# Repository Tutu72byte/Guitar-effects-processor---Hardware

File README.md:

Complete hardware development of an embedded music signal processing module (Guitar Effect Pedal) from structural block diagram to circuit schematic,
pcb design and generation of manufacturing files using KiCad. The projects consists of:

1) Library Creation: Created dedicated project libraries (TIE2026.kicad_sym and TIE2026.pretty) containing custom schematic symbols and footprints.

2) Schematic design: The circuit diagram contains a Microcontroller, SPI Flash Memory, ADC/DAC audio processing stages,
   an interactive touchscreen interface and a switching power supply (9V in, 5V and 3.3V converters and regulators and a 2.5V bias).
   Incorporated specific JTAG and power rail test pads for hardware debugging.

3) PCB Topology & Stack-up: Configured a 4-layer board stack-up (1.6mm total thickness)
   featuring controlled trace spacing (0.1mm) and a dedicated internal ground plane split between analog ground (GND_A)
   and digital ground (GND), thus managing a low-noise layout by segregating the analog circuitry onto the analog ground plane linked via the 10m-Ohms shunt R28.

4) Routing for High-Speed Signals & Impedance Control: Implemented single-ended 50 Ohms data lines for the Flash
   memory and 100 Ohms differential lines for the video interface.

5) Manufacturing Output: Generated industry-standard production packages, including extended
   Gerber files, Drill files, a Pick-and-Place component file and a Bill of Materials (BOM).

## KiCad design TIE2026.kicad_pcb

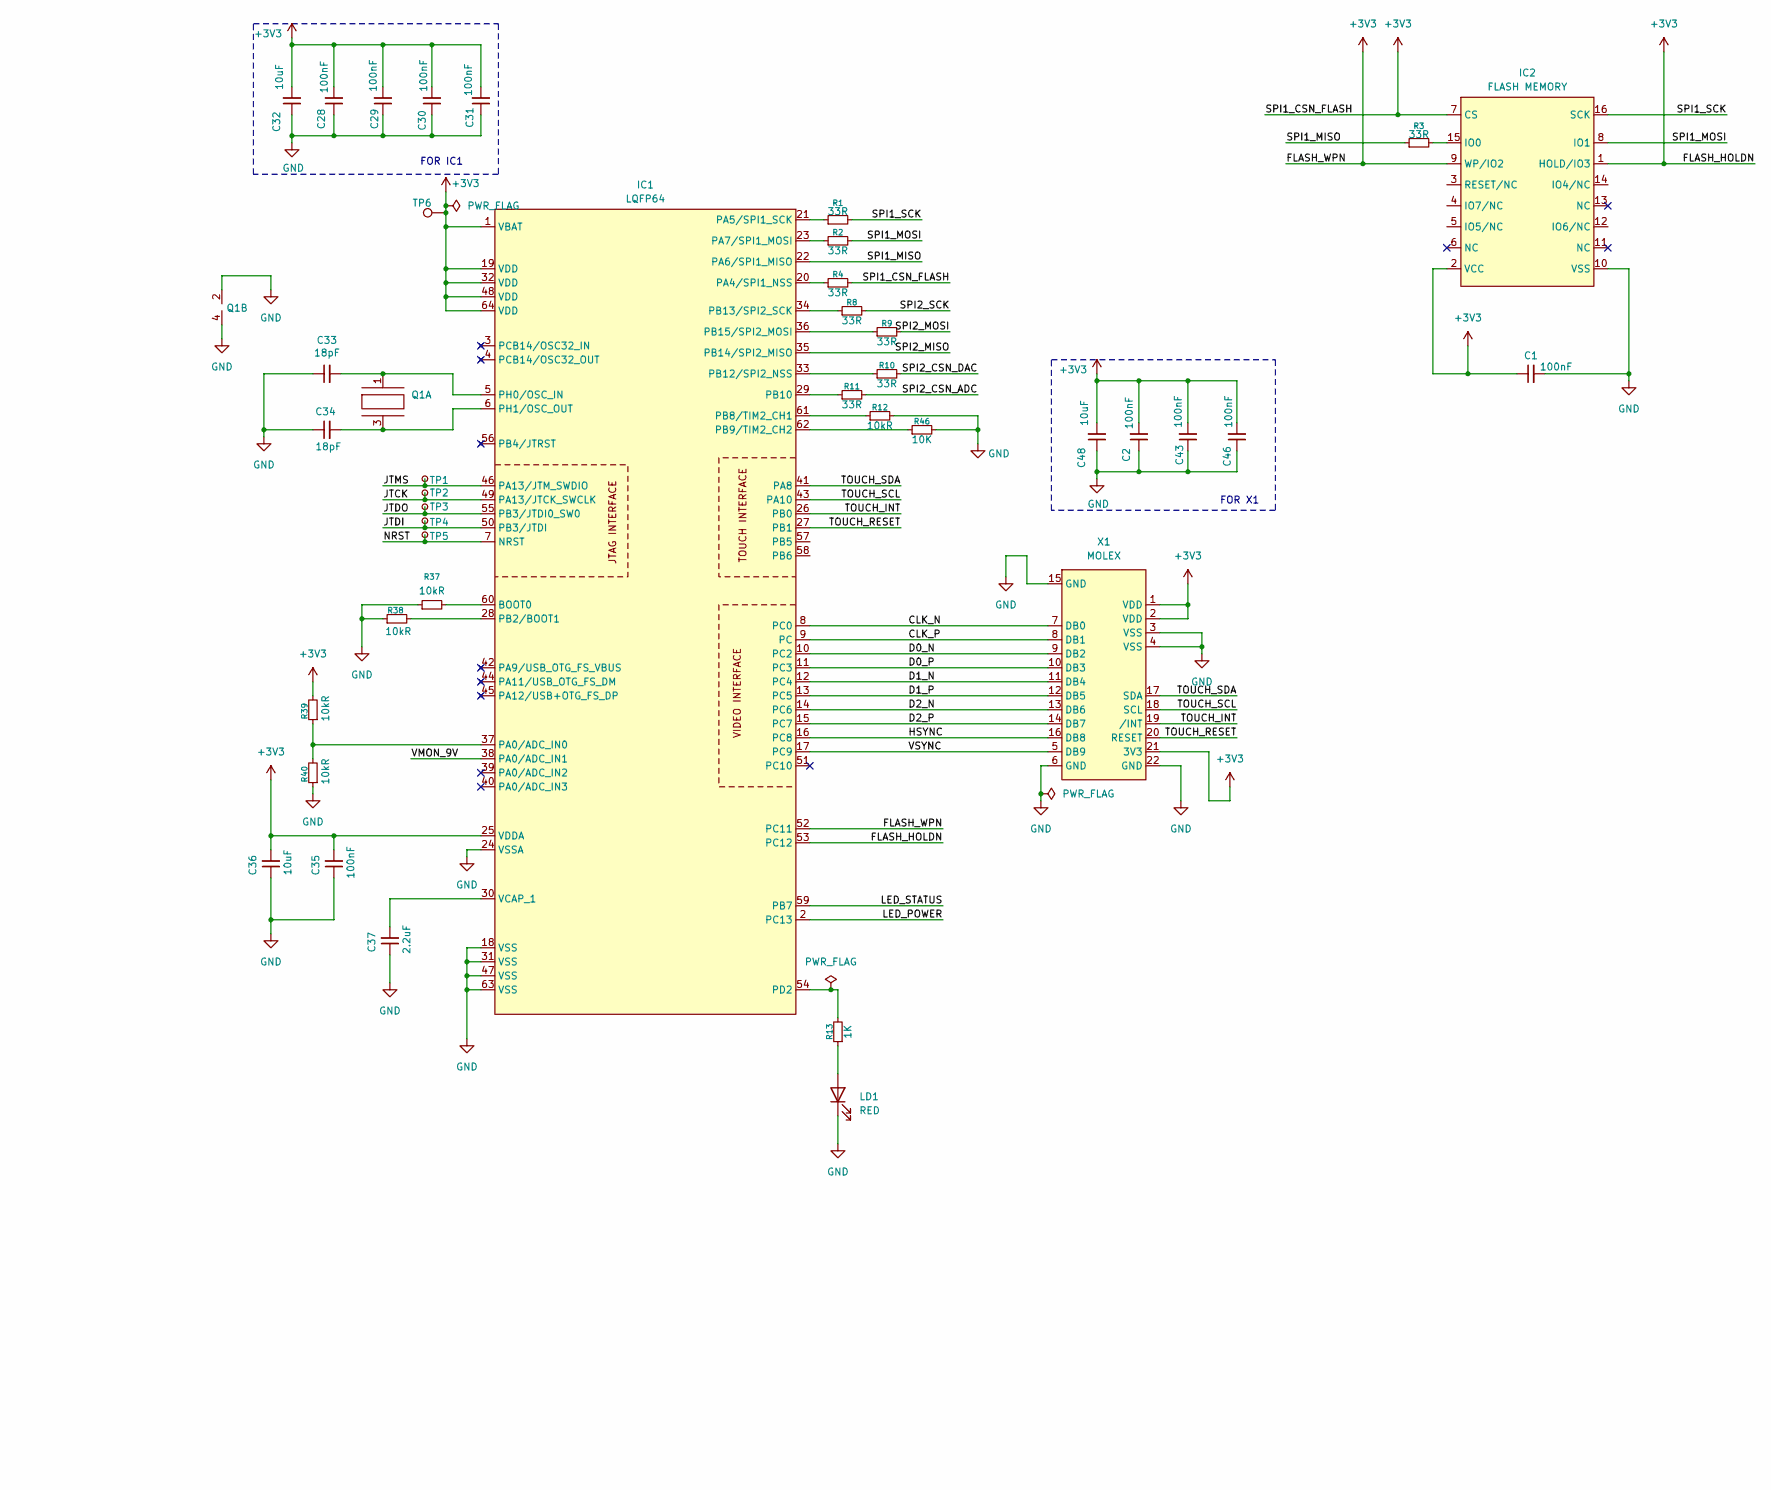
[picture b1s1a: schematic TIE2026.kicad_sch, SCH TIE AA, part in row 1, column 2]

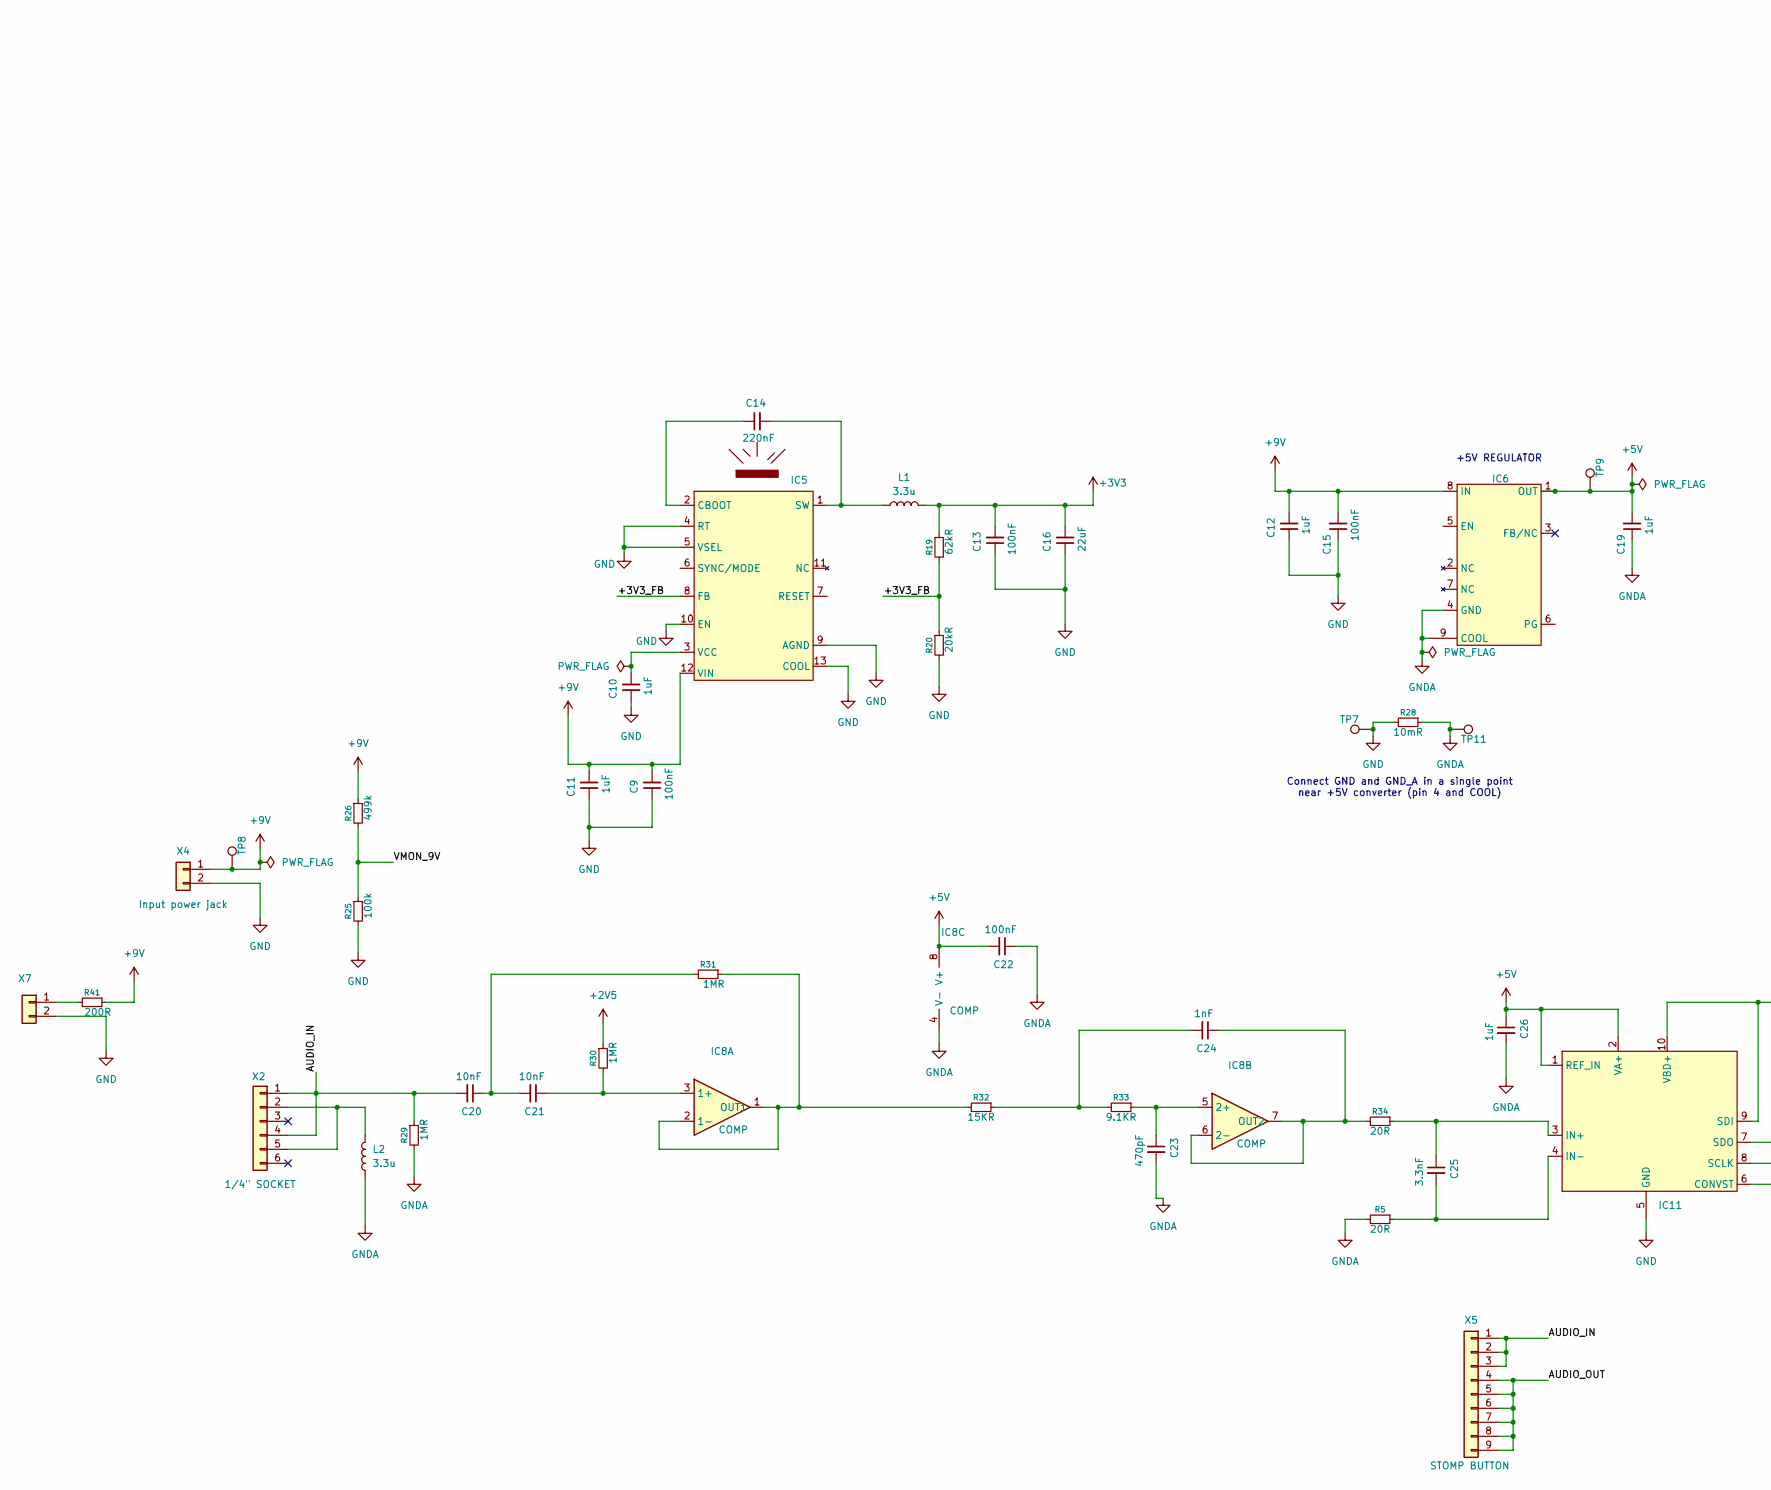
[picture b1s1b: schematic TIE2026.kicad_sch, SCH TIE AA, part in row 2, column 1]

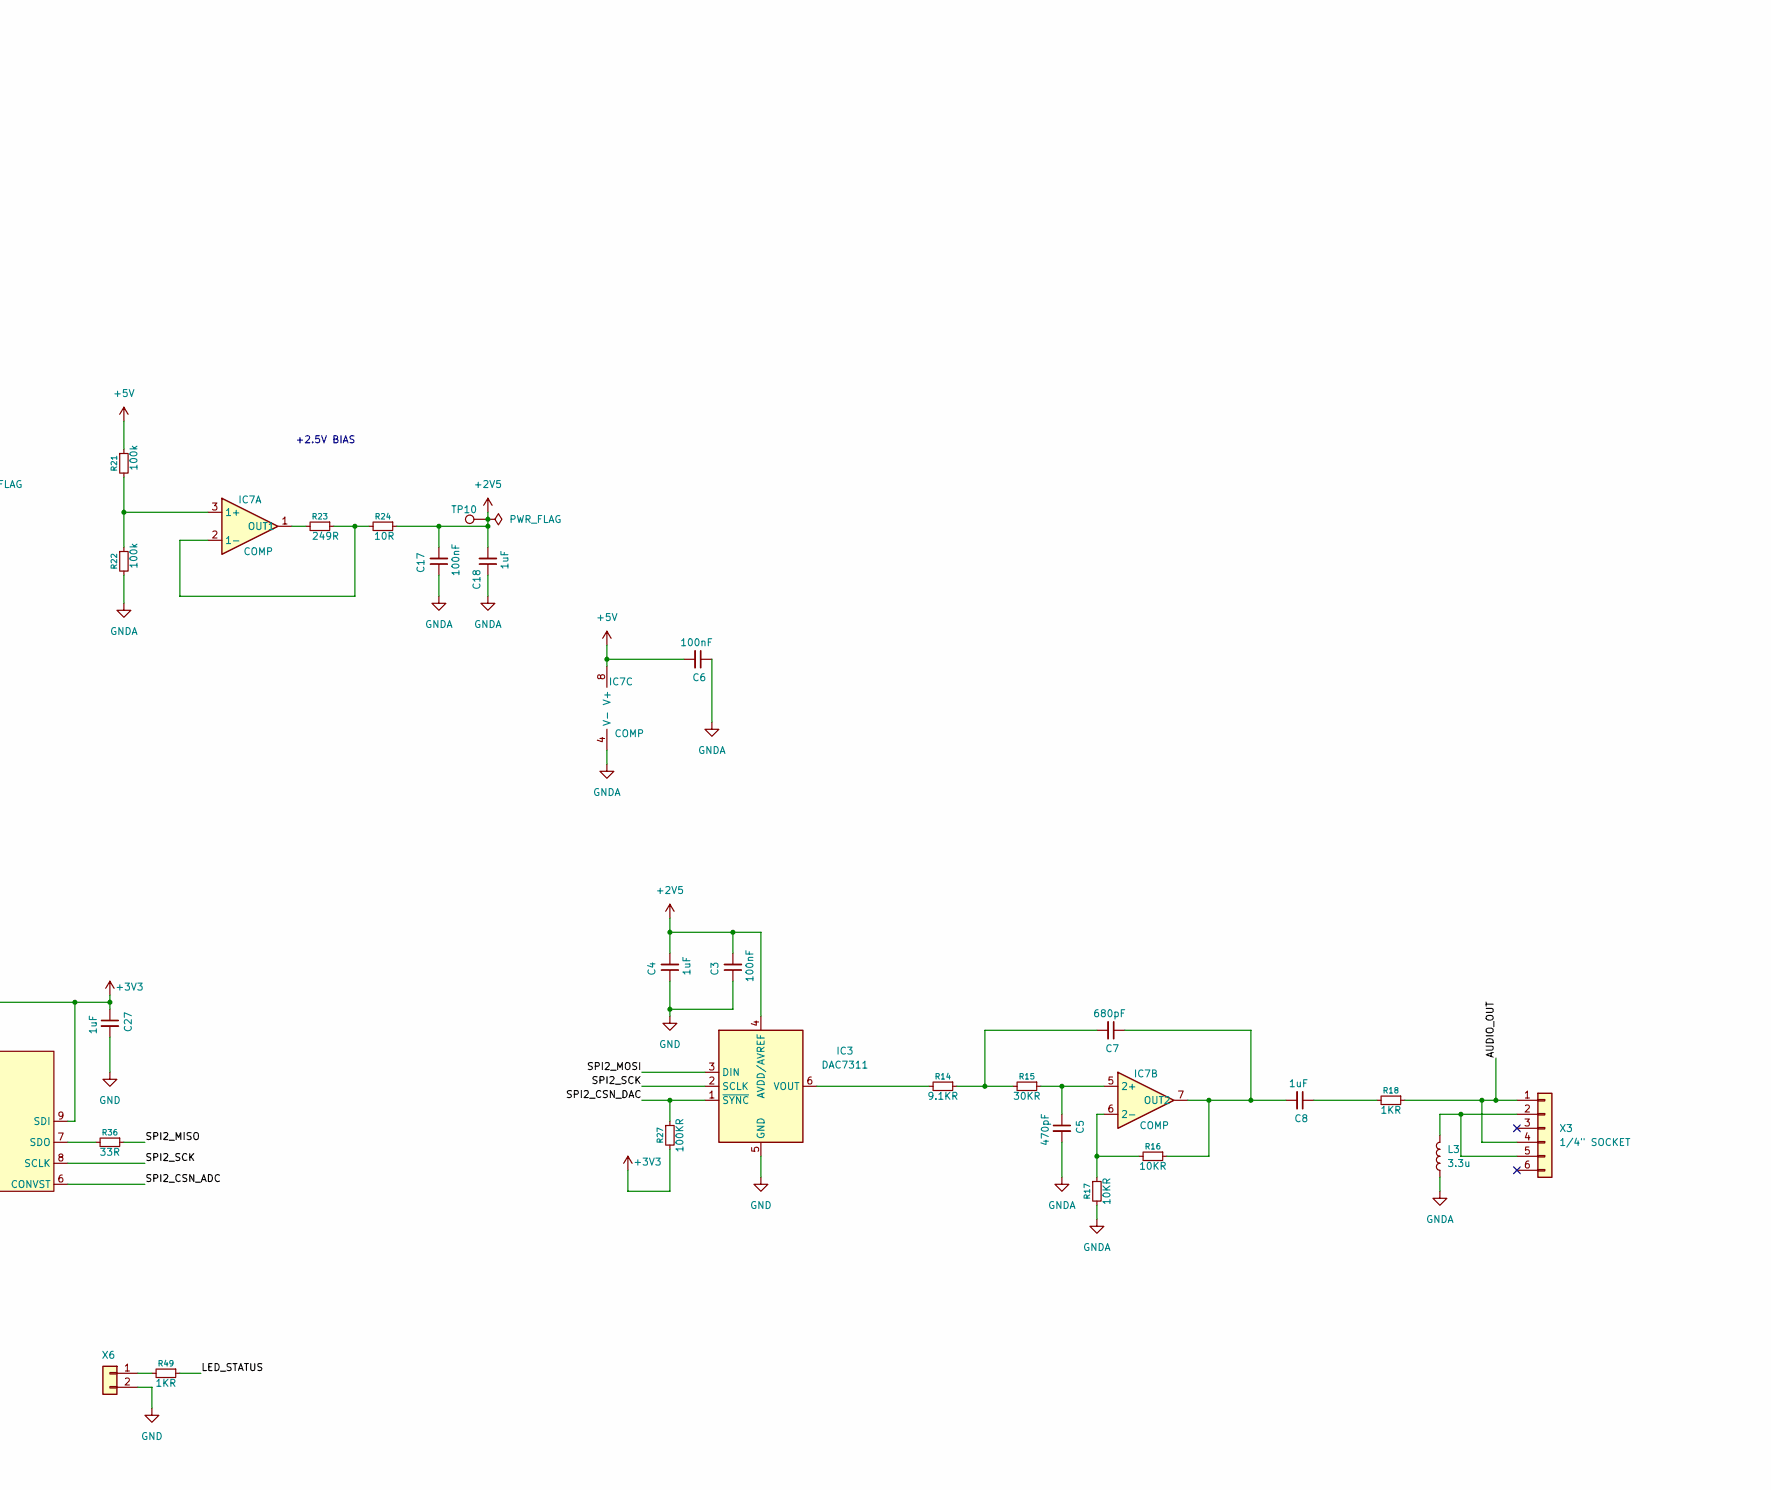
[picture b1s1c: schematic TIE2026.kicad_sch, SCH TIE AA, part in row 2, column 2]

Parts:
C1, C2, C3, C6, C9, C13, C15, C17, C22, C28, C29, C30, C31, C35, C43, C46: 100nF; C_01005_0402Metric
C4, C10, C12, C18, C19, C26, C27: 1uF; C_0805_2012Metric
C5, C23: 470pF; C_01005_0402Metric
C7: 680pF; C_0201_0603Metric
C8: 1uF; C_1206_3216Metric
C11: 1uF; C_1210_3225Metric
C14: 220nF; C_0201_0603Metric
C16: 22uF; C_1210_3225Metric
C20, C21: 10nF; C_0201_0603Metric
C24: 1nF; C_01005_0402Metric
C25: 3.3nF; C_01005_0402Metric
C32, C36, C48: 10uF; C_0201_0603Metric
C33, C34: 18pF; C_0201_0603Metric
C37: 2.2uF; C_0201_0603Metric
IC1: LQFP64; IC1_LQFP64
IC2: FLASH MEMORY; IC2_SO16
IC3: DAC7311; IC3_TSOP6
IC5: IC5_WSON12
IC6: TPS74501PQWDRBRQ1; IC6_SONB
IC7, IC8: COMP; 8AB_PDS08
IC11: IC11_VSSOP
L1: 3.3u; L1_NRS5040
L2, L3: 3.3u; L_0201_0603Metric
LD1: RED; LD1_PLCC
Q1: Q1_NX3225
R1, R2, R3, R4, R8, R9, R10, R11, R36: 33R; R_0402_1005Metric
R5, R34: 20R; R_0402_1005Metric
R12, R37, R38, R39, R40: 10kR; R_0805_2012Metric
R13: 1K; R_0201_0603Metric
R14, R33: 9.1KR; R_0201_0603Metric
R15: 30KR; R_0201_0603Metric
R16, R17: 10KR; R_0805_2012Metric
R18, R49: 1KR; R_0201_0603Metric
R19: 62kR; R_0402_1005Metric
R20: 20kR; R_0402_1005Metric
R21, R22, R25: 100k; R_0201_0603Metric
R23: 249R; R_0201_0603Metric
R24: 10R; R_0201_0603Metric
R26: 499k; R_0201_0603Metric
R27: 100KR; R_0201_0603Metric
R28: 10mR; R_0805_2012Metric
R29, R30, R31: 1MR; R_0805_2012Metric
R32: 15KR; R_0201_0603Metric
R41: 200R; R_0201_0603Metric
R46: 10K; R_0805_2012Metric
TP1, TP2, TP3, TP4, TP5, TP6, TP7, TP8, TP9, TP10, TP11: TEST_POINT_TIE2026
X1: MOLEX; X1_MOLEX
X2, X3: 1/4" SOCKET; QInch_Jack
X4: Input power jack; ADC_021_3
X5: STOMP BUTTON; XC5_MC71101
X6, X7: CONN_2.54; PinHeader_1x02_P2.54mm_Vertical

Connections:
+2V5: C3.2, C4.2, C17.2, C18.2, IC3.4 (AVDD/AVREF), R24.1, R30.1, TP10.1
+3V3: C1.1, C2.2, C13.2, C16.2, C27.1, C28.2, C29.2, C30.2, C31.2, C32.2, C35.2, C36.2, C43.2, C46.2, C48.2, IC1.1 (VBAT), IC1.19 (VDD), IC1.25 (VDDA), IC1.32 (VDD), IC1.48 (VDD), IC1.52 (PC11), IC1.53 (PC12), IC1.64 (VDD), IC2.1 (HOLD/IO3), IC2.2 (VCC), IC2.7 (CS), IC2.9 (WP/IO2), IC11.9 (SDI), IC11.10 (VBD+), L1.2, R4.2, R19.1, R27.2, R39.2, TP6.1, X1.1 (VDD), X1.2 (VDD), X1.21 (3V3)
+5V: C6.2, C19.2, C22.2, C26.1, IC6.1 (OUT), IC7.8 (V+), IC8.8 (V+), IC11.1 (REF_IN), IC11.2 (VA+), R21.1, TP9.1
+9V: C9.2, C11.2, C12.2, C15.2, IC5.12 (VIN), IC6.8 (IN), R26.1, R41.1, TP8.1, X4.1
/+3V3_FB: IC5.8 (FB), R19.2, R20.1
/AUDIO_IN: C20.2, R29.1, X2.1, X2.4, X5.1, X5.2, X5.3
/AUDIO_OUT: R18.1, X3.1, X3.4, X5.4, X5.5, X5.6, X5.7, X5.8, X5.9
/CLK_N: IC1.8 (PC0), X1.7 (DB0)
/CLK_P: IC1.9 (PC), X1.8 (DB1)
/D0_N: IC1.10 (PC2), X1.9 (DB2)
/D0_P: IC1.11 (PC3), X1.10 (DB3)
/D1_N: IC1.12 (PC4), X1.11 (DB4)
/D1_P: IC1.13 (PC5), X1.12 (DB5)
/D2_N: IC1.14 (PC6), X1.13 (DB6)
/D2_P: IC1.15 (PC7), X1.14 (DB7)
/HSYNC: IC1.16 (PC8), X1.16 (DB8)
/JTCK: IC1.49 (PA13/JTCK_SWCLK), TP2.1
/JTDI: IC1.50 (PB3/JTDI), TP4.1
/JTDO: IC1.55 (PB3/JTDI0_SW0), TP3.1
/JTMS: IC1.46 (PA13/JTM_SWDIO), TP1.1
/LED_POWER: IC1.2 (PC13)
/LED_STATUS: IC1.59 (PB7), R49.1
/NRST: IC1.7 (NRST), TP5.1
/SPI1_MISO: IC1.22 (PA6/SPI1_MISO), R3.1
/SPI1_MOSI: IC2.8 (IO1), R2.2
/SPI1_SCK: IC2.16 (SCK), R1.2
/SPI2_CSN_ADC: IC11.6 (CONVST), R11.2
/SPI2_CSN_DAC: IC3.1 (~SYNC), R10.2, R27.1
/SPI2_MISO: IC1.35 (PB14/SPI2_MISO), R36.1
/SPI2_MOSI: IC3.3 (DIN), R9.2
/SPI2_SCK: IC3.2 (SCLK), IC11.8 (SCLK), R8.2
/TOUCH_INT: IC1.26 (PB0), X1.19 (/INT)
/TOUCH_RESET: IC1.27 (PB1), X1.20 (RESET)
/TOUCH_SCL: IC1.43 (PA10), X1.18 (SCL)
/TOUCH_SDA: IC1.41 (PA8), X1.17 (SDA)
/VMON_9V: IC1.38 (PA0/ADC_IN1), R25.1, R26.2
/VSYNC: IC1.17 (PC9), X1.5 (DB9)
GND: C1.2, C2.1, C3.1, C4.1, C9.1, C10.1, C11.1, C12.1, C13.1, C15.1, C16.1, C27.2, C28.1, C29.1, C30.1, C31.1, C32.1, C33.1, C34.1, C35.1, C36.1, C37.1, C43.1, C46.1, C48.1, IC1.18 (VSS), IC1.24 (VSSA), IC1.31 (VSS), IC1.47 (VSS), IC1.63 (VSS), IC2.10 (VSS), IC3.5 (GND), IC5.4 (RT), IC5.5 (VSEL), IC5.9 (AGND), IC5.10 (EN), IC5.13 (COOL), IC11.5 (GND), LD1.1 (K), Q1.2, Q1.4, R12.2, R20.2, R25.2, R28.2, R37.1, R38.1, R40.1, R46.2, TP7.1, X1.3 (VSS), X1.4 (VSS), X1.6 (GND), X1.15 (GND), X1.22 (GND), X4.2, X6.2, X7.2
GNDA: C5.2, C6.1, C17.1, C18.1, C19.1, C22.1, C23.2, C26.2, IC6.4 (GND), IC6.9 (COOL), IC7.4 (V-), IC8.4 (V-), L2.1, L3.1, R5.2, R17.2, R22.2, R28.1, R29.2, TP11.1
unnamed: C7.2, R14.1, R15.2
unnamed: C8.1, R18.2
unnamed: C20.1, C21.2, R31.2
unnamed: C24.2, R32.1, R33.2
unnamed: IC1.60 (BOOT0), R37.2
unnamed: IC1.37 (PA0/ADC_IN0), R39.1, R40.2
unnamed: IC1.20 (PA4/SPI1_NSS), R4.1
unnamed: IC1.21 (PA5/SPI1_SCK), R1.1
unnamed: IC1.23 (PA7/SPI1_MOSI), R2.1
unnamed: IC1.28 (PB2/BOOT1), R38.2
unnamed: IC1.61 (PB8/TIM2_CH1), R12.1
unnamed: IC1.62 (PB9/TIM2_CH2), R46.1
unnamed: IC1.29 (PB10), R11.1
unnamed: IC1.33 (PB12/SPI2_NSS), R10.1
unnamed: IC1.34 (PB13/SPI2_SCK), R8.1
unnamed: IC1.36 (PB15/SPI2_MOSI), R9.1
unnamed: IC1.54 (PD2), R13.2
unnamed: C33.2, IC1.5 (PH0/OSC_IN), Q1.1
unnamed: C34.2, IC1.6 (PH1/OSC_OUT), Q1.3
unnamed: C37.2, IC1.30 (VCAP_1)
unnamed: IC2.15 (IO0), R3.2
unnamed: IC3.6 (VOUT), R14.2
unnamed: C14.1, IC5.2 (CBOOT)
unnamed: C14.2, IC5.1 (SW), L1.1
unnamed: C10.2, IC5.3 (VCC)
unnamed: IC7.3 (1+), R21.2, R22.1
unnamed: IC7.2 (1-), R23.1, R24.2
unnamed: IC7.1 (OUT1), R23.2
unnamed: C5.1, IC7.5 (2+), R15.1
unnamed: IC7.6 (2-), R16.2, R17.1
unnamed: C7.1, C8.2, IC7.7 (OUT2), R16.1
unnamed: C21.1, IC8.3 (1+), R30.2
unnamed: IC8.1 (OUT1), IC8.2 (1-), R31.1, R32.2
unnamed: C23.1, IC8.5 (2+), R33.1
unnamed: C24.1, IC8.6 (2-), IC8.7 (OUT2), R34.2
unnamed: C25.1, IC11.3 (IN+), R34.1
unnamed: C25.2, IC11.4 (IN-), R5.1
unnamed: IC11.7 (SDO), R36.2
unnamed: LD1.2 (A), R13.1
unnamed: L2.2, X2.2, X2.5
unnamed: L3.2, X3.2, X3.5
unnamed: R49.2, X6.1
unnamed: R41.2, X7.1

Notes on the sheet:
+5V REGULATOR
FOR X1
FOR IC1
Connect GND and GND_A in a single point near +5V converter (pin 4 and COOL)
+2.5V BIAS

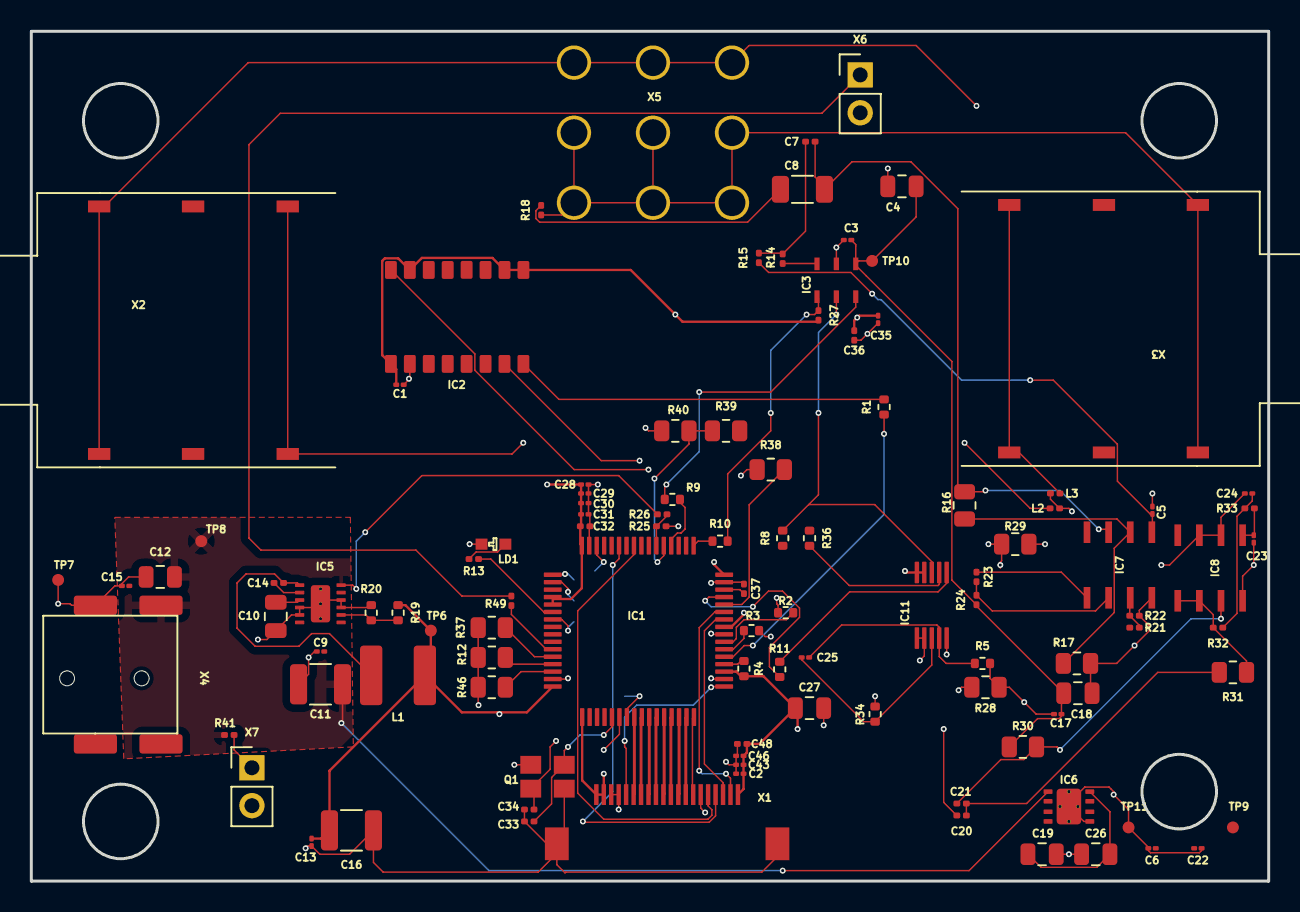
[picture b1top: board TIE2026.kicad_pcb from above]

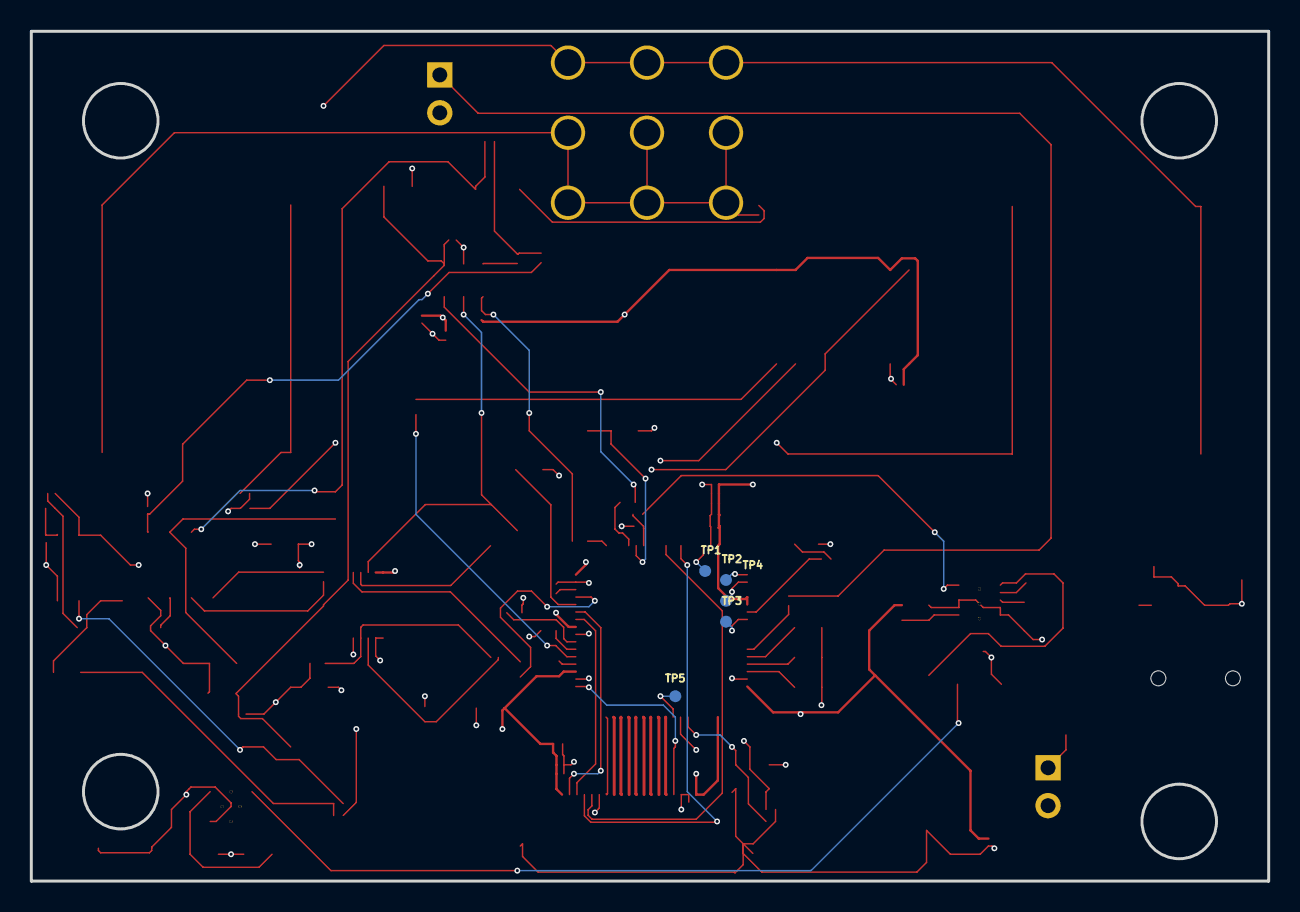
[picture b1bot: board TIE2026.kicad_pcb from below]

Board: 4 copper layers, 83.0 x 57.0 mm, 111 parts (5 on the bottom side), 81 nets.

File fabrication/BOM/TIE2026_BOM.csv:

"Reference","Qty","Value","DNP","Exclude from BOM","Exclude from Board","Footprint","Datasheet"
"C1,C2,C3,C6,C9,C13,C15,C17,C22,C28,C29,C30,C31,C35,C43,C46","16","100nF","","","","Capacitor_SMD:C_01005_0402Metric","~"
"C4,C10,C12,C18,C19,C26,C27","7","1uF","","","","Capacitor_SMD:C_0805_2012Metric","~"
"C5,C23","2","470pF","","","","Capacitor_SMD:C_01005_0402Metric","~"
"C7","1","680pF","","","","Capacitor_SMD:C_0201_0603Metric","~"
"C8","1","1uF","","","","Capacitor_SMD:C_1206_3216Metric","~"
"C11","1","1uF","","","","Capacitor_SMD:C_1210_3225Metric","~"
"C14","1","220nF","","","","Capacitor_SMD:C_0201_0603Metric","~"
"C16","1","22uF","","","","Capacitor_SMD:C_1210_3225Metric","~"
"C20,C21","2","10nF","","","","Capacitor_SMD:C_0201_0603Metric","~"
"C24","1","1nF","","","","Capacitor_SMD:C_01005_0402Metric","~"
"C25","1","3.3nF","","","","Capacitor_SMD:C_01005_0402Metric","~"
"C32,C36,C48","3","10uF","","","","Capacitor_SMD:C_0201_0603Metric","~"
"C33,C34","2","18pF","","","","Capacitor_SMD:C_0201_0603Metric","~"
"C37","1","2.2uF","","","","Capacitor_SMD:C_0201_0603Metric","~"
"IC1","1","LQFP64","","","","TIE2026:IC1_LQFP64",""
"IC2","1","FLASH MEMORY","","","","TIE2026:IC2_SO16",""
"IC3","1","DAC7311","","","","TIE2026:IC3_TSOP6","https://www.ti.com/lit/ds/symlink/dac5311.pdf"
"IC5","1","~","","","","TIE2026:IC5_WSON12",""
"IC6","1","TPS74501PQWDRBRQ1","","","","TIE2026:IC6_SONB",""
"IC7,IC8","2","COMP","","","","TIE2026:8AB_PDS08","~"
"IC11","1","~","","","","TIE2026:IC11_VSSOP",""
"L1","1","3.3u","","","","TIE2026:L1_NRS5040","~"
"L2,L3","2","3.3u","","","","Inductor_SMD:L_0201_0603Metric","~"
"LD1","1","RED","","","","TIE2026:LD1_PLCC","~"
"Q1","1","~","","","","TIE2026:Q1_NX3225",""
"R1,R2,R3,R4,R8,R9,R10,R11,R36","9","33R","","","","Resistor_SMD:R_0402_1005Metric","~"
"R5,R34","2","20R","","","","Resistor_SMD:R_0402_1005Metric","~"
"R12,R37,R38,R39,R40","5","10kR","","","","Resistor_SMD:R_0805_2012Metric","~"
"R13","1","1K","","","","Resistor_SMD:R_0201_0603Metric","~"
"R14,R33","2","9.1KR","","","","Resistor_SMD:R_0201_0603Metric","~"
"R15","1","30KR","","","","Resistor_SMD:R_0201_0603Metric","~"
"R16,R17","2","10KR","","","","Resistor_SMD:R_0805_2012Metric","~"
"R18,R49","2","1KR","","","","Resistor_SMD:R_0201_0603Metric","~"
"R19","1","62kR","","","","Resistor_SMD:R_0402_1005Metric","~"
"R20","1","20kR","","","","Resistor_SMD:R_0402_1005Metric","~"
"R21,R22,R25","3","100k","","","","Resistor_SMD:R_0201_0603Metric","~"
"R23","1","249R","","","","Resistor_SMD:R_0201_0603Metric","~"
"R24","1","10R","","","","Resistor_SMD:R_0201_0603Metric","~"
"R26","1","499k","","","","Resistor_SMD:R_0201_0603Metric","~"
"R27","1","100KR","","","","Resistor_SMD:R_0201_0603Metric","~"
"R28","1","10mR","","","","Resistor_SMD:R_0805_2012Metric","~"
"R29,R30,R31","3","1MR","","","","Resistor_SMD:R_0805_2012Metric","~"
"R32","1","15KR","","","","Resistor_SMD:R_0201_0603Metric","~"
"R41","1","200R","","","","Resistor_SMD:R_0201_0603Metric","~"
"R46","1","10K","","","","Resistor_SMD:R_0805_2012Metric","~"
"TP1,TP2,TP3,TP4,TP5,TP6,TP7,TP8,TP9,TP10,TP11","11","~","","","","TIE2026:TEST_POINT_TIE2026","~"
"X1","1","MOLEX","","","","TIE2026:X1_MOLEX",""
"X2,X3","2","1/4"" SOCKET","","","","TIE2026:QInch_Jack","~"
"X4","1","Input power jack","","","","TIE2026:ADC_021_3","~"
"X5","1","STOMP BUTTON","","","","TIE2026:XC5_MC71101","~"
"X6,X7","2","CONN_2.54","","","","Connector_PinHeader_2.54mm:PinHeader_1x02_P2.54mm_Vertical","~"

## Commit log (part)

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2026-05-31 Initial clean push TIE2026
2026-05-31 Add project overview for embedded music signal processor
    Documented the complete hardware development process for an embedded music signal processing module, including library creation, schematic design, PCB topology, routing for high-speed signals, and ma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
